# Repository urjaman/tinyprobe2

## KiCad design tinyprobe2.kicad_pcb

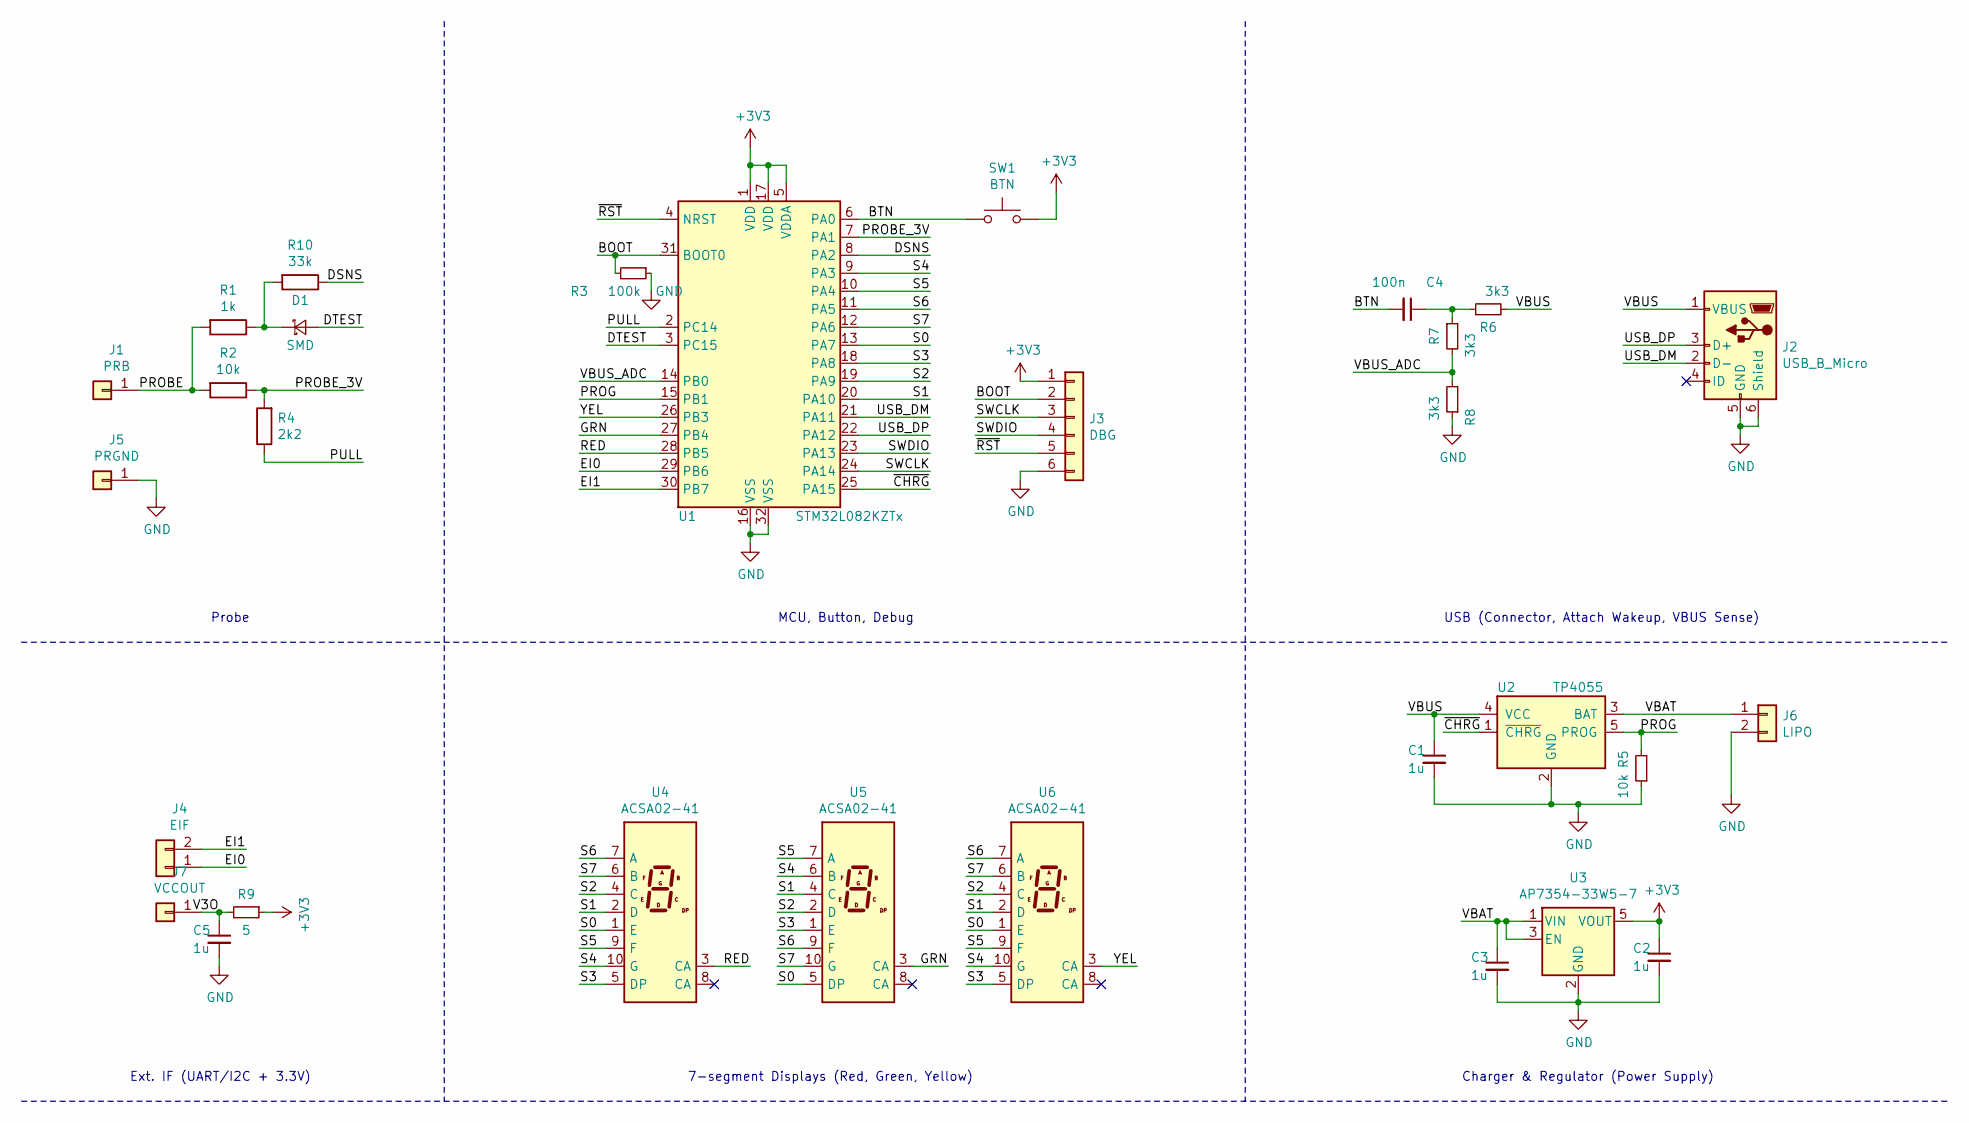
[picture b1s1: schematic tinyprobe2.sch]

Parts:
C1, C2, C3, C5: 1u; C_0603_1608Metric_Pad1.05x0.95mm_HandSolder
C4: 100n; C_0603_1608Metric_Pad1.05x0.95mm_HandSolder
D1: SMD; D_SOD-323_HandSoldering
J1: PRB; PinHeader_1x01_P2.54mm_Vertical
J2: USB_B_Micro; USB_Micro-B_GCT_USB3076-30-A
J3: DBG; PinHeader_1x06_P2.00mm_Vertical
J4: EIF; PinHeader_1x02_P2.54mm_Vertical
J5: PRGND; PinHeader_1x01_P2.54mm_Vertical
J6: LIPO; PinHeader_1x02_P2.54mm_Vertical
J7: VCCOUT; PinHeader_1x01_P2.54mm_Vertical
R1: 1k; R_0603_1608Metric_Pad1.05x0.95mm_HandSolder
R2, R5: 10k; R_0603_1608Metric_Pad1.05x0.95mm_HandSolder
R3: 100k; R_0603_1608Metric_Pad1.05x0.95mm_HandSolder
R4: 2k2; R_0603_1608Metric_Pad1.05x0.95mm_HandSolder
R6, R7, R8: 3k3; R_0603_1608Metric_Pad1.05x0.95mm_HandSolder
R9: 5; R_0603_1608Metric_Pad1.05x0.95mm_HandSolder
R10: 33k; R_0603_1608Metric_Pad1.05x0.95mm_HandSolder
SW1: BTN; SW_PUSH_6mm
U1: STM32L082KZTx; LQFP-32_7x7mm_P0.8mm
U2: TP4055; SOT-23-5
U3: AP7354-33W5-7; SOT-23-5
U4, U5, U6: ACSA02-41; KCSC02-105

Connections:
+3V3: C2.1, J3.1, R9.1, SW1.2, U1.1 (VDD), U1.5 (VDDA), U1.17 (VDD), U3.5 (VOUT)
/BOOT: J3.2, R3.2, U1.31 (BOOT0)
/BTN: C4.2, SW1.1, U1.6 (PA0)
/DSNS: R10.1, U1.8 (PA2)
/DTEST: D1.2 (A), U1.3 (PC15)
/EI0: J4.1, U1.29 (PB6)
/EI1: J4.2, U1.30 (PB7)
/GRN: U1.27 (PB4), U5.3 (CA)
/PROBE: J1.1, R1.2, R2.2
/PROBE_3V: R2.1, R4.2, U1.7 (PA1)
/PROG: R5.2, U1.15 (PB1), U2.5 (PROG)
/PULL: R4.1, U1.2 (PC14)
/RED: U1.28 (PB5), U4.3 (CA)
/S0: U1.13 (PA7), U4.1 (E), U5.5 (DP), U6.1 (E)
/S1: U1.20 (PA10), U4.2 (D), U5.4 (C), U6.2 (D)
/S2: U1.19 (PA9), U4.4 (C), U5.2 (D), U6.4 (C)
/S3: U1.18 (PA8), U4.5 (DP), U5.1 (E), U6.5 (DP)
/S4: U1.9 (PA3), U4.10 (G), U5.6 (B), U6.10 (G)
/S5: U1.10 (PA4), U4.9 (F), U5.7 (A), U6.9 (F)
/S6: U1.11 (PA5), U4.7 (A), U5.9 (F), U6.7 (A)
/S7: U1.12 (PA6), U4.6 (B), U5.10 (G), U6.6 (B)
/SWCLK: J3.3, U1.24 (PA14)
/SWDIO: J3.4, U1.23 (PA13)
/USB_DM: J2.2 (D-), U1.21 (PA11)
/USB_DP: J2.3 (D+), U1.22 (PA12)
/V3O: C5.1, J7.1, R9.2
/VBAT: C3.1, J6.1, U2.3 (BAT), U3.1 (VIN), U3.3 (EN)
/VBUS: C1.1, J2.1 (VBUS), R6.2, U2.4 (VCC)
/VBUS_ADC: R7.2, R8.2, U1.14 (PB0)
/YEL: U1.26 (PB3), U6.3 (CA)
/~CHRG: U1.25 (PA15), U2.1 (~CHRG)
/~RST: J3.5, U1.4 (NRST)
GND: C1.2, C2.2, C3.2, C5.2, J2.5 (GND), J2.6 (Shield), J3.6, J5.1, J6.2, R3.1, R5.1, R8.1, U1.16 (VSS), U1.32 (VSS), U2.2 (GND), U3.2 (GND)
unnamed: C4.1, R6.1, R7.1
unnamed: D1.1 (K), R1.1, R10.2

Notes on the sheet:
Probe
MCU, Button, Debug
Ext. IF (UART/I2C + 3.3V)
7-segment Displays (Red, Green, Yellow)
Charger & Regulator (Power Supply)
USB (Connector, Attach Wakeup, VBUS Sense)

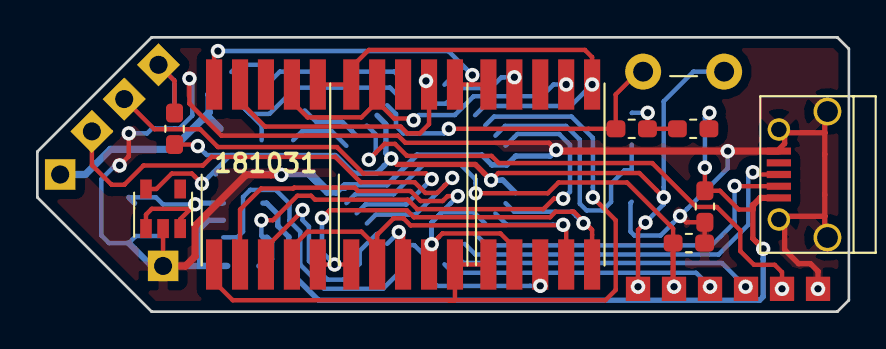
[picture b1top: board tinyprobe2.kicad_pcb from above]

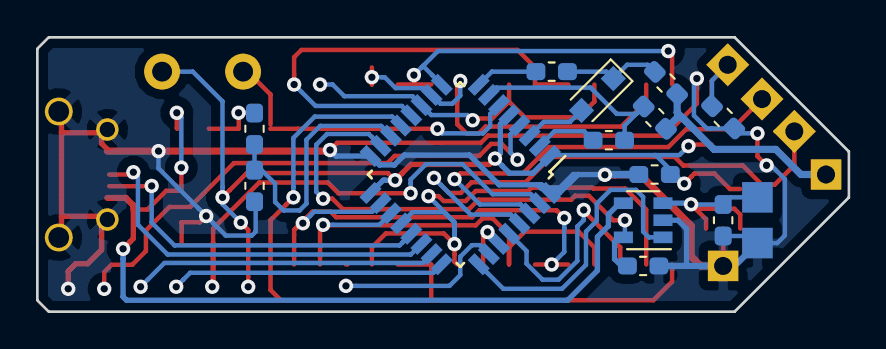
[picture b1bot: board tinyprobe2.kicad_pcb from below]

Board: 2 copper layers, 45.1 x 15.2 mm, 30 parts (14 on the bottom side), 35 nets.

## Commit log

2018-10-25 First commit from the 7-hour stream
2018-10-25 forgot license
2018-10-27 last rev with the resistors
2018-10-31 days of tuning it
2018-11-08 add a copying file and idk what else
